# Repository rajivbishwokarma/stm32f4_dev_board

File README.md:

# STM32F405RGT6 Development Board KiCAD Design Files

## Introduction
This repository contains a development board for STM32F405RGT6 microcontroller.

## Circuit Schematic

## PCB and 3D View

## Microcontroller

## Buck Converter and SWD Interface

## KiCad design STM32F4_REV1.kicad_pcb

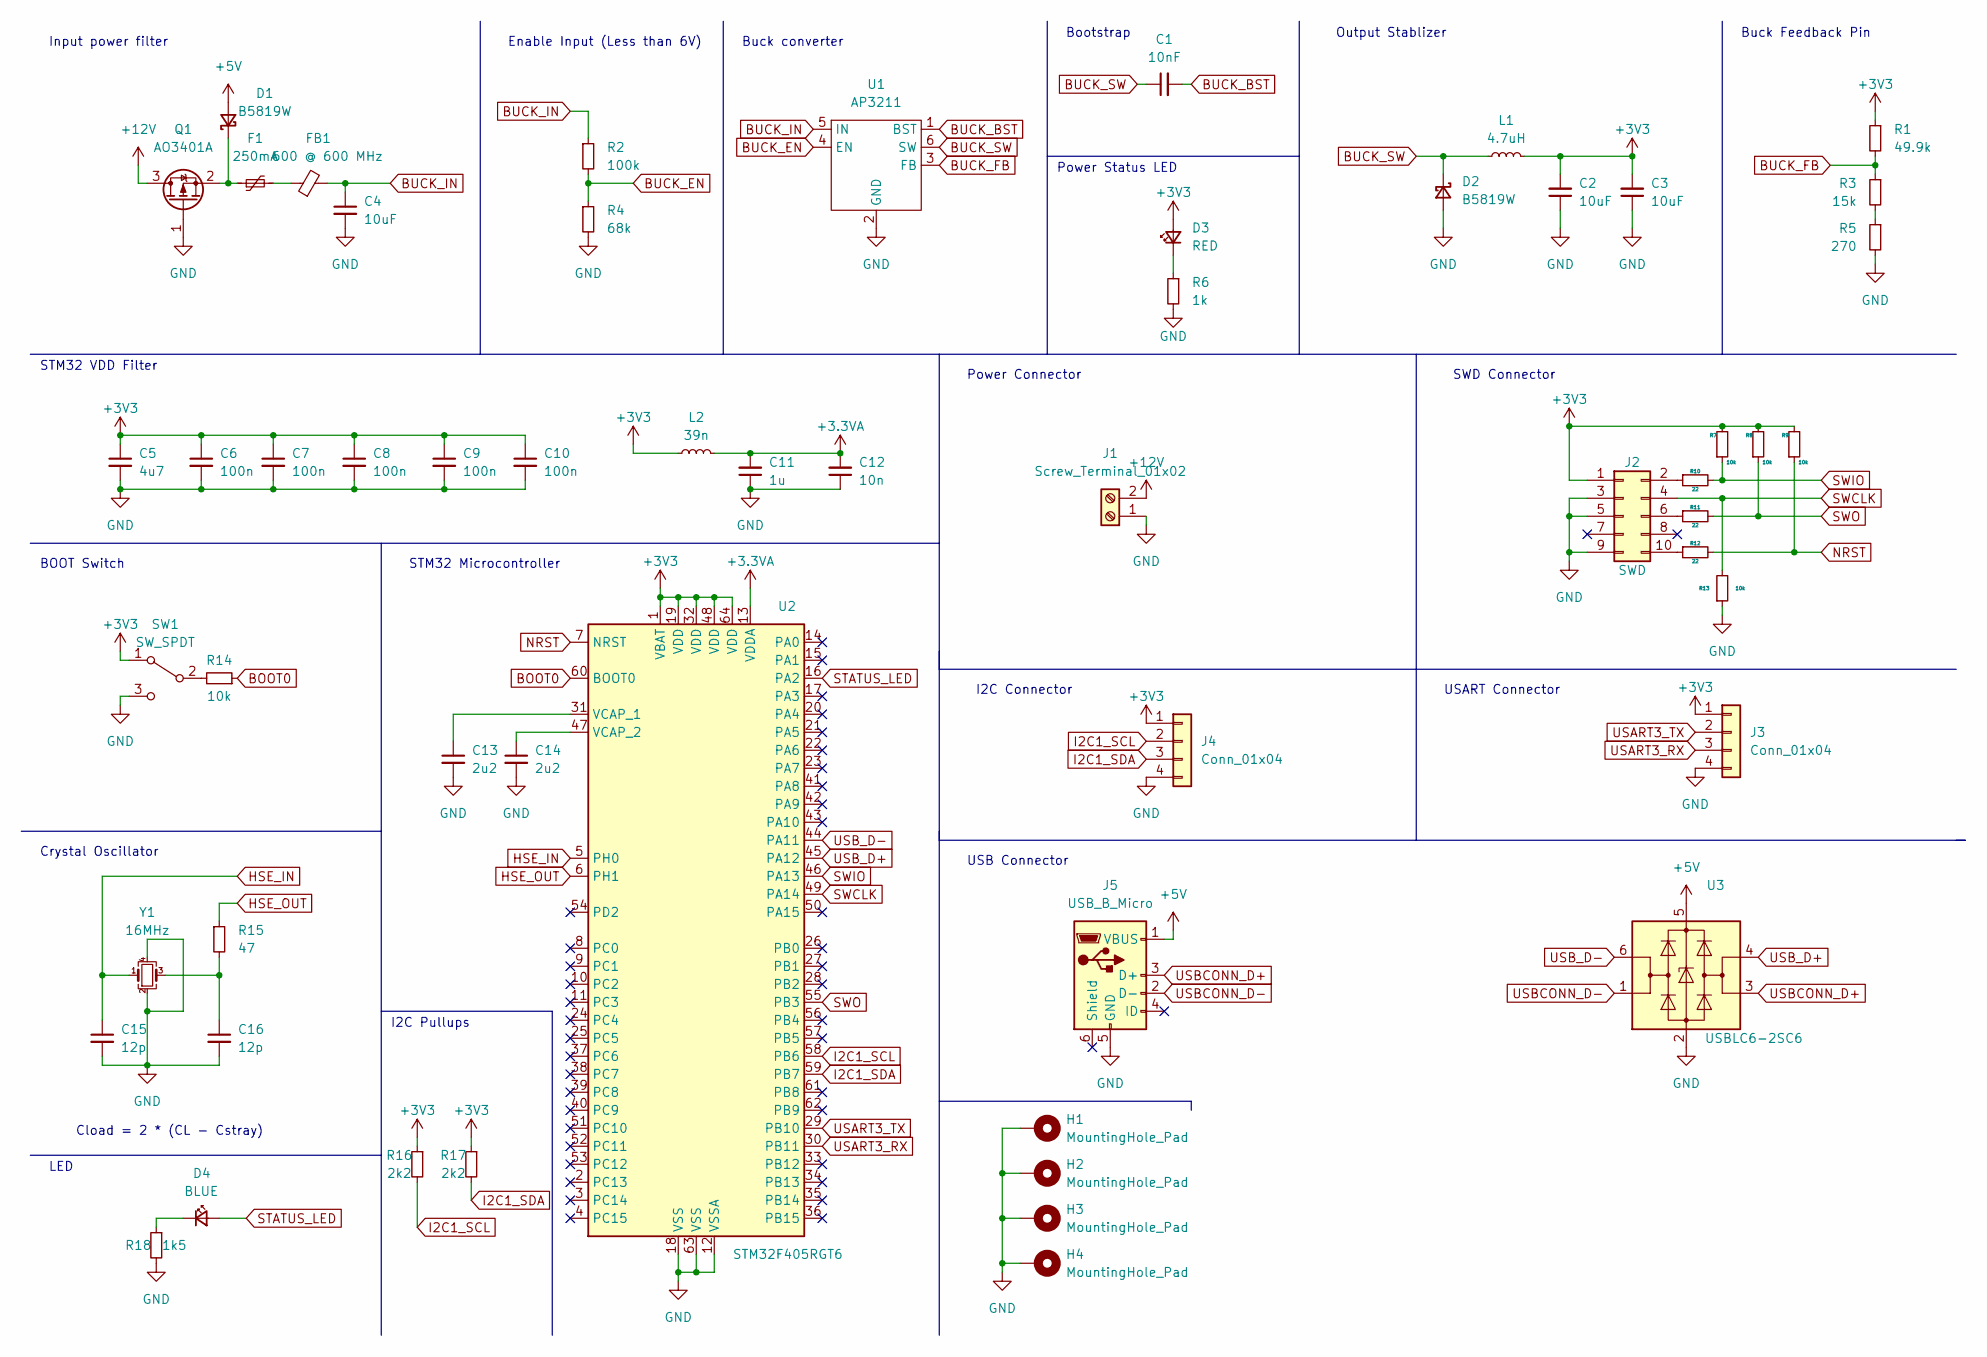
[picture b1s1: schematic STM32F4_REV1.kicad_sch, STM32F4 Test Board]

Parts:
C1: 10nF; C_0603_1608Metric; LCSC Part # C282516
C2, C3, C4: 10uF; C_1206_3216Metric; LCSC Part # C165101
C5: 4u7; C_0805_2012Metric; LCSC Part # C131057
C6, C7, C8, C9, C10: 100n; C_0402_1005Metric; LCSC Part # C106204
C11: 1u; C_0402_1005Metric; LCSC Part # C106254
C12: 10n; C_0402_1005Metric; LCSC Part # C783637
C13, C14: 2u2; C_0805_2012Metric; LCSC Part # C105486
C15, C16: 12p; C_0402_1005Metric; LCSC Part # C147414
D1, D2: B5819W; D_SOD-123; LCSC Part # C908224
D3: RED; LED_0603_1608Metric; LCSC Part # C84263
D4: BLUE; LED_0603_1608Metric; LCSC Part # C375575
F1: 250mA; Fuse_1206_3216Metric; LCSC Part # C182446
FB1: 600 @ 600 MHz; L_0805_2012Metric; LCSC Part # C82155
H1, H2, H3, H4: MountingHole_Pad; MountingHole_4.3mm_M4_Pad_Via
J1: Screw_Terminal_01x02; TerminalBlock_Phoenix_PT-1,5-2-3.5-H_1x02_P3.50mm_Horizontal; LCSC Part # C395882
J2: SWD; PinHeader_2x05_P1.27mm_Vertical_SMD; LCSC Part # C5142425
J3, J4: Conn_01x04; Molex_PicoBlade_53048-0410_1x04_P1.25mm_Horizontal
J5: USB_B_Micro; USB_Micro-B_Amphenol_10103594-0001LF_Horizontal; LCSC Part # C598519
L1: 4.7uH; L_Sunlord_MWSA0518_5.4x5.2mm; LCSC Part # C408349
L2: 39n; L_0402_1005Metric; LCSC Part # C142231
Q1: AO3401A; SOT-23; LCSC Part # C347476
R1: 49.9k; R_0603_1608Metric; LCSC Part # C365177
R2: 100k; R_0603_1608Metric; LCSC Part # C217279
R3: 15k; R_0603_1608Metric; LCSC Part # C285208
R4: 68k; R_0603_1608Metric; LCSC Part # C177676
R5: 270; R_0603_1608Metric; LCSC Part # C209092
R6: 1k; R_0603_1608Metric; LCSC Part # C216905
R7, R8, R9, R13, R14: 10k; R_0402_1005Metric; LCSC Part # C406733
R10, R11, R12: 22; R_0402_1005Metric; LCSC Part # C102894
R15: 47; R_0402_1005Metric; LCSC Part # C11930
R16, R17: 2k2; R_0402_1005Metric; LCSC Part # C114762
R18: 1k5; R_0603_1608Metric; LCSC Part # C140221
SW1: SW_SPDT; SW_SPDT_CK-JS102011SAQN; LCSC Part # C221660
U1: AP3211; SOT-23-6; LCSC Part # C14259
U2: STM32F405RGT6; LQFP-64_10x10mm_P0.5mm; LCSC Part # C15742
U3: USBLC6-2SC6; SOT-23-6; LCSC Part # C7519
Y1: 16MHz; Crystal_SMD_3225-4Pin_3.2x2.5mm; LCSC Part # C13738

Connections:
+3.3VA: C11.2, C12.2, L2.2, U2.13 (VDDA)
+3V3: C2.2, C3.2, C5.1, C6.1, C7.1, C8.1, C9.1, C10.1, D3.2 (A), J2.1, J3.1, J4.1, L1.2, L2.1, R1.1, R7.2, R8.2, R9.2, R16.1, R17.1, SW1.1 (A), U2.1 (VBAT), U2.19 (VDD), U2.32 (VDD), U2.48 (VDD), U2.64 (VDD)
+5V: D1.2 (A), J5.1 (VBUS), U3.5 (VBUS)
+12V: J1.2, Q1.3 (D)
BOOT0: R14.1, U2.60 (BOOT0)
BUCK_BST: C1.2, U1.1 (BST)
BUCK_EN: R2.2, R4.1, U1.4 (EN)
BUCK_FB: R1.2, R3.1, U1.3 (FB)
BUCK_IN: C4.1, FB1.2, R2.1, U1.5 (IN)
BUCK_SW: C1.1, D2.1 (K), L1.1, U1.6 (SW)
GND: C2.1, C3.1, C4.2, C5.2, C6.2, C7.2, C8.2, C9.2, C10.2, C11.1, C12.1, C13.2, C14.2, C15.2, C16.2, D2.2 (A), H1.1, H2.1, H3.1, H4.1, J1.1, J2.3, J2.5, J2.9, J3.4, J4.4, J5.5 (GND), Q1.1 (G), R4.2, R5.2, R6.2, R13.1, R18.2, SW1.3 (C), U1.2 (GND), U2.12 (VSSA), U2.18 (VSS), U2.63 (VSS), U3.2 (GND), Y1.2, Y1.4
HSE_IN: C15.1, U2.5 (PH0), Y1.1
HSE_OUT: R15.1, U2.6 (PH1)
I2C1_SCL: J4.2, R16.2, U2.58 (PB6)
I2C1_SDA: J4.3, R17.2, U2.59 (PB7)
NRST: R9.1, R12.2, U2.7 (NRST)
unnamed: C13.1, U2.31 (VCAP_1)
unnamed: C14.1, U2.47 (VCAP_2)
unnamed: C16.1, R15.2, Y1.3
unnamed: D1.1 (K), F1.1, Q1.2 (S)
unnamed: D3.1 (K), R6.1
unnamed: D4.1 (K), R18.1
unnamed: F1.2, FB1.1
unnamed: J2.2, R10.1
unnamed: J2.6, R11.1
unnamed: J2.10, R12.1
unnamed: R3.2, R5.1
unnamed: R14.2, SW1.2 (B)
STATUS_LED: D4.2 (A), U2.16 (PA2)
SWCLK: J2.4, R13.2, U2.49 (PA14)
SWIO: R7.1, R10.2, U2.46 (PA13)
SWO: R8.1, R11.2, U2.55 (PB3)
USART3_RX: J3.3, U2.30 (PB11)
USART3_TX: J3.2, U2.29 (PB10)
USBCONN_D+: J5.3 (D+), U3.3 (I/O2)
USBCONN_D-: J5.2 (D-), U3.1 (I/O1)
USB_D+: U2.45 (PA12), U3.4 (I/O2)
USB_D-: U2.44 (PA11), U3.6 (I/O1)

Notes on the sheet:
STM32 VDD Filter
Cload = 2 * (CL - Cstray)
I2C Pullups
STM32 Microcontroller
Input power filter
USART Connector
I2C Connector
Crystal Oscillator
SWD Connector
Buck Feedback Pin
Buck converter
Power Status LED
Output Stablizer
Bootstrap
LED
Enable Input (Less than 6V)
USB Connector
Power Connector
BOOT Switch

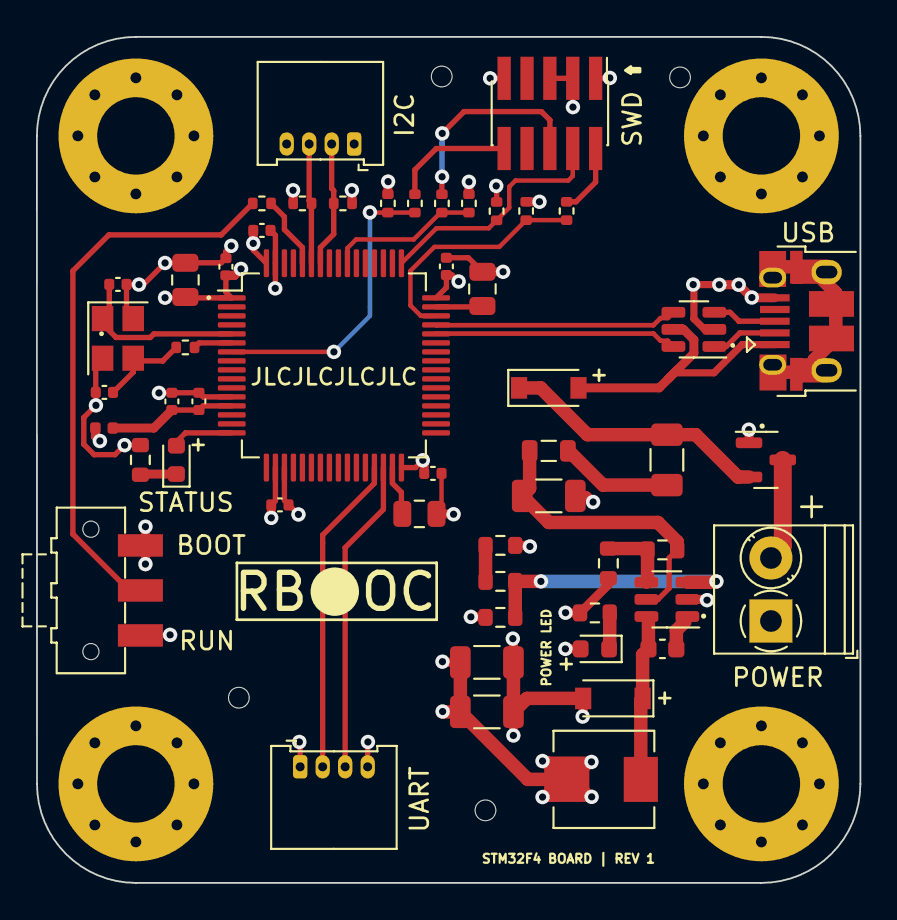
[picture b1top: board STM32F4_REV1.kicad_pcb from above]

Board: 4 copper layers, 45.8 x 47.0 mm, 57 parts (0 on the bottom side), 38 nets.

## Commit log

2023-02-02 Update READM
2023-02-02 Add complete files
2023-02-02 Add schematic PDF and images
